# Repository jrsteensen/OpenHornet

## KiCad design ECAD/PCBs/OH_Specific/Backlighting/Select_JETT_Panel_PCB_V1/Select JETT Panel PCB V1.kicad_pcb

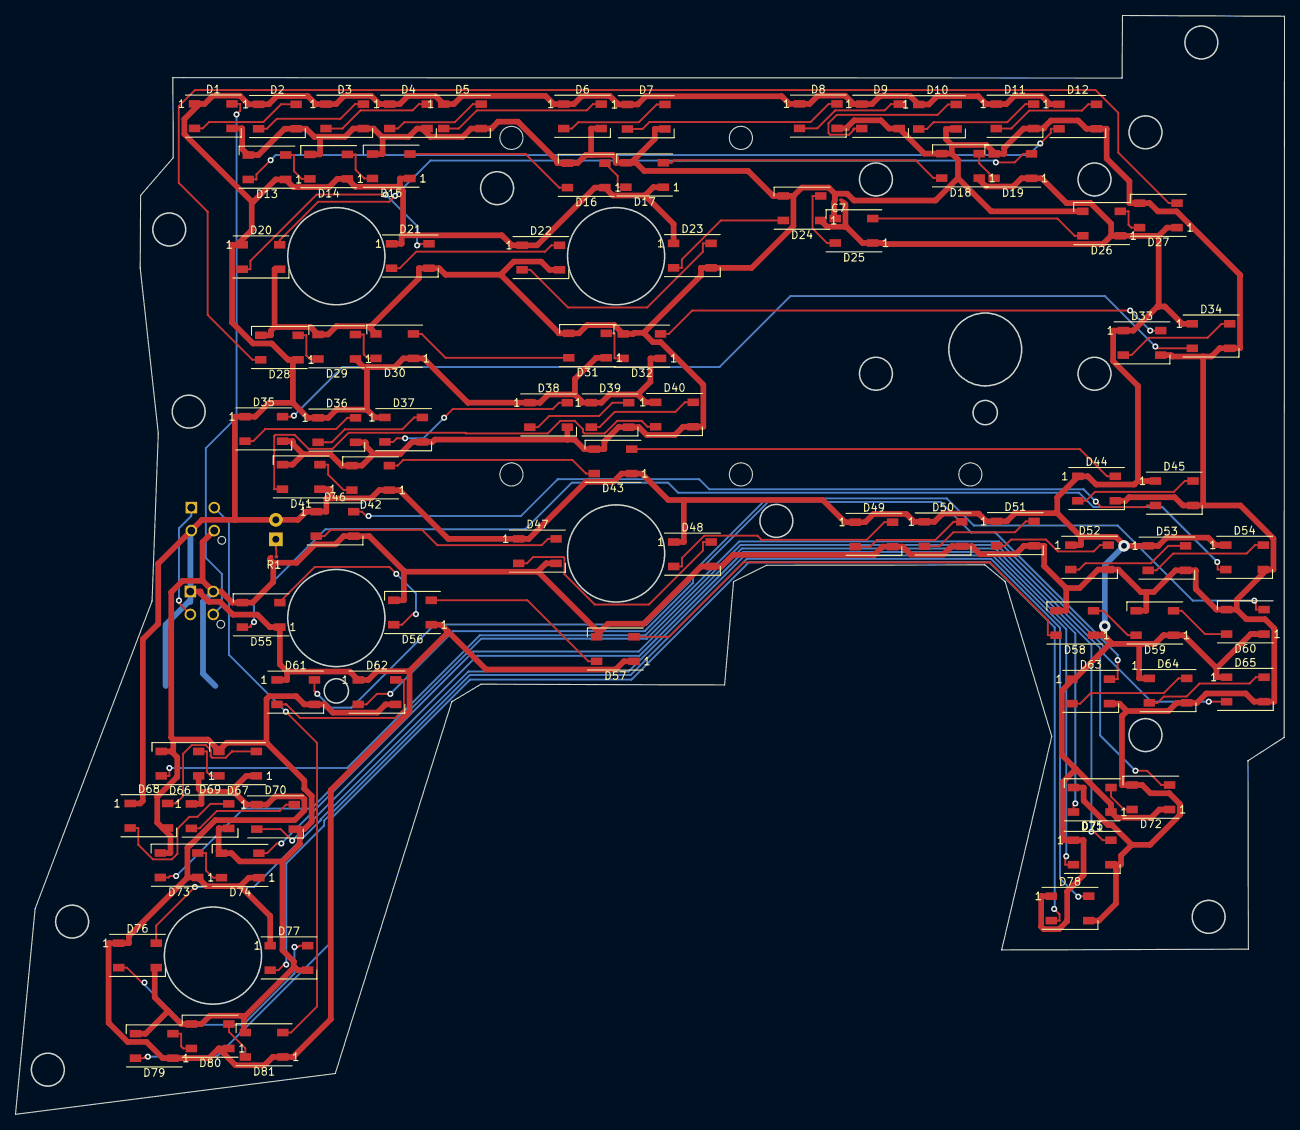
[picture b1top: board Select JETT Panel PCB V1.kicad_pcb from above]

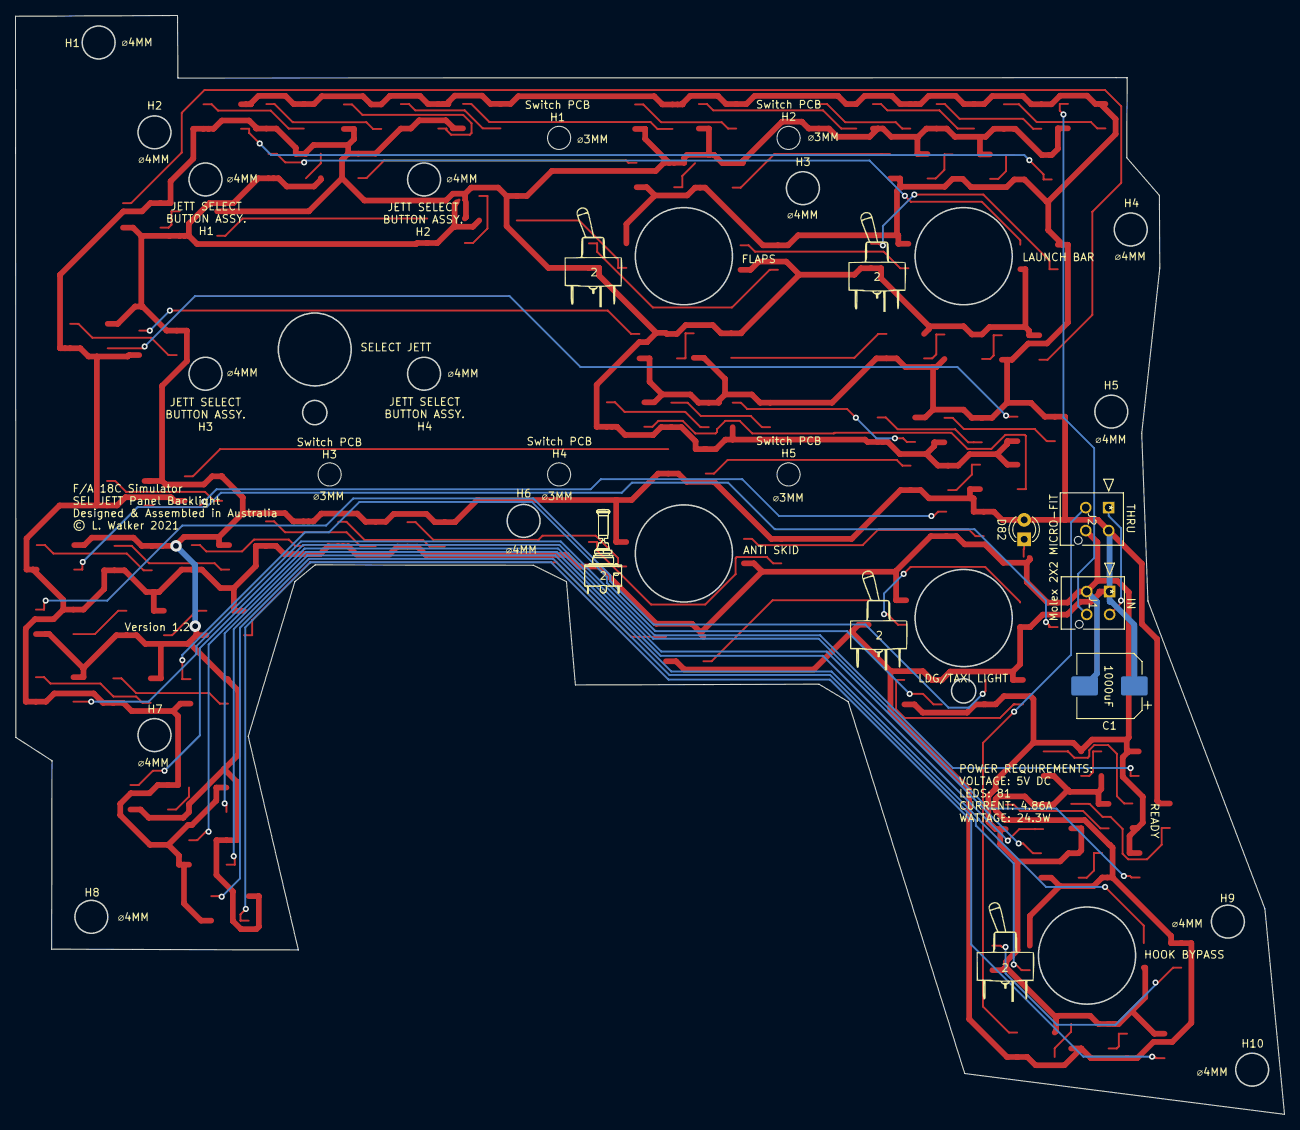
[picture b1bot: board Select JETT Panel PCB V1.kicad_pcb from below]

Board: 2 copper layers, 165.9 x 143.7 mm, 92 parts (9 on the bottom side), 86 nets.

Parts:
C1: C_Polarized; CP_Elec_8x10
C7: C; C_0201_0603Metric
D1, D2, D3, D4, D5, D6, D7, D8, D9, D10, D11, D12, D13, D14, D15, D16, D17, D18, D19, D20, D21, D22, D23, D24, D25, D26, D27, D28, D29, D30, D31, D32, D33, D34, D35, D36, D37, D38, D39, D40, D41, D42, D43, D44, D45, D46, D47, D48, D49, D50, D51, D52, D53, D54, D55, D56, D57, D58, D59, D60, D61, D62, D63, D64, D65, D66, D67, D68, D69, D70, D71, D72, D73, D74, D75, D76, D77, D78, D79, D80, D81: WS2812B; LED_WS2812B_PLCC4_5.0x5.0mm_P3.2mm
D82: LED; LED_D3.0mm
G1, G2, G3, G5: LOGO; 631HToggle
G4: LOGO; S2ALToggle
J1, J2: Conn_01x04_Female; Molex_MicroFit_2X2
R1: R; R_0201_0603Metric

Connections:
/DATAIN: D1.4, J1.4
/DATALOOP: J1.2, J2.1
/DATAOUT: D81.2, J2.3
/LED+5V: C1.1, C7.1, D1.1, D2.1, D3.1, D4.1, D5.1, D6.1, D7.1, D8.1, D9.1, D10.1, D11.1, D12.1, D13.1, D14.1, D15.1, D16.1, D17.1, D18.1, D19.1, D20.1, D21.1, D22.1, D23.1, D24.1, D25.1, D26.1, D27.1, D28.1, D29.1, D30.1, D31.1, D32.1, D33.1, D34.1, D35.1, D36.1, D37.1, D38.1, D39.1, D40.1, D41.1, D42.1, D43.1, D44.1, D45.1, D46.1, D47.1, D48.1, D49.1, D50.1, D51.1, D52.1, D53.1, D54.1, D55.1, D56.1, D57.1, D58.1, D59.1, D60.1, D61.1, D62.1, D63.1, D64.1, D65.1, D66.1, D67.1, D68.1, D69.1, D70.1, D71.1, D72.1, D73.1, D74.1, D75.1, D76.1, D77.1, D78.1, D79.1, D80.1, D81.1, D82.2, J1.1, J2.2
/LEDGND: C1.2, C7.2, D1.3, D2.3, D3.3, D4.3, D5.3, D6.3, D7.3, D8.3, D9.3, D10.3, D11.3, D12.3, D13.3, D14.3, D15.3, D16.3, D17.3, D18.3, D19.3, D20.3, D21.3, D22.3, D23.3, D24.3, D25.3, D26.3, D27.3, D28.3, D29.3, D30.3, D31.3, D32.3, D33.3, D34.3, D35.3, D36.3, D37.3, D38.3, D39.3, D40.3, D41.3, D42.3, D43.3, D44.3, D45.3, D46.3, D47.3, D48.3, D49.3, D50.3, D51.3, D52.3, D53.3, D54.3, D55.3, D56.3, D57.3, D58.3, D59.3, D60.3, D61.3, D62.3, D63.3, D64.3, D65.3, D66.3, D67.3, D68.3, D69.3, D70.3, D71.3, D72.3, D73.3, D74.3, D75.3, D76.3, D77.3, D78.3, D79.3, D80.3, D81.3, J1.3, J2.4, R1.2
unnamed: D1.2, D2.4
unnamed: D2.2, D3.4
unnamed: D3.2, D4.4
unnamed: D4.2, D5.4
unnamed: D5.2, D6.4
unnamed: D6.2, D7.4
unnamed: D7.2, D8.4
unnamed: D8.2, D9.4
unnamed: D10.2, D11.4
unnamed: D9.2, D10.4
unnamed: D11.2, D12.4
unnamed: D12.2, D13.4
unnamed: D13.2, D14.4
unnamed: D14.2, D15.4
unnamed: D15.2, D16.4
unnamed: D16.2, D17.4
unnamed: D17.2, D18.4
unnamed: D18.2, D19.4
unnamed: D19.2, D20.4
unnamed: D20.2, D21.4
unnamed: D21.2, D22.4
unnamed: D22.2, D23.4
unnamed: D23.2, D24.4
unnamed: D24.2, D25.4
unnamed: D25.2, D26.4
unnamed: D26.2, D27.4
unnamed: D27.2, D28.4
unnamed: D28.2, D29.4
unnamed: D29.2, D30.4
unnamed: D30.2, D31.4
unnamed: D31.2, D32.4
unnamed: D32.2, D33.4
unnamed: D33.2, D34.4
unnamed: D34.2, D35.4
unnamed: D35.2, D36.4
unnamed: D36.2, D37.4
unnamed: D37.2, D38.4
unnamed: D38.2, D39.4
unnamed: D39.2, D40.4
unnamed: D40.2, D41.4
unnamed: D41.2, D42.4
unnamed: D42.2, D43.4
unnamed: D43.2, D44.4
unnamed: D44.2, D45.4
unnamed: D45.2, D46.4
unnamed: D46.2, D47.4
unnamed: D47.2, D48.4
unnamed: D48.2, D49.4
unnamed: D49.2, D50.4
unnamed: D50.2, D51.4
unnamed: D51.2, D52.4
unnamed: D52.2, D53.4
unnamed: D53.2, D54.4
unnamed: D54.2, D55.4
unnamed: D55.2, D56.4
unnamed: D56.2, D57.4
unnamed: D57.2, D58.4
unnamed: D58.2, D59.4
unnamed: D59.2, D60.4
unnamed: D60.2, D61.4
unnamed: D61.2, D62.4
unnamed: D62.2, D63.4
unnamed: D63.2, D64.4
unnamed: D64.2, D65.4
unnamed: D65.2, D66.4
unnamed: D66.2, D67.4
unnamed: D67.2, D68.4
unnamed: D68.2, D69.4
unnamed: D69.2, D70.4
unnamed: D70.2, D71.4
unnamed: D71.2, D72.4
unnamed: D72.2, D73.4
unnamed: D73.2, D74.4
unnamed: D74.2, D75.4
unnamed: D75.2, D76.4
unnamed: D76.2, D77.4
unnamed: D77.2, D78.4
unnamed: D78.2, D79.4
unnamed: D79.2, D80.4
unnamed: D80.2, D81.4
unnamed: D82.1, R1.1

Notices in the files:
ECAD/PCBs/OH_Specific/Backlighting/Select_JETT_Panel_PCB_V1/Select JETT Panel PCB V1.kicad_pcb:
© L. Walker 2021
parts and their libraries:
Copyright 2016 Accelerated Designs. All rights reserved.
